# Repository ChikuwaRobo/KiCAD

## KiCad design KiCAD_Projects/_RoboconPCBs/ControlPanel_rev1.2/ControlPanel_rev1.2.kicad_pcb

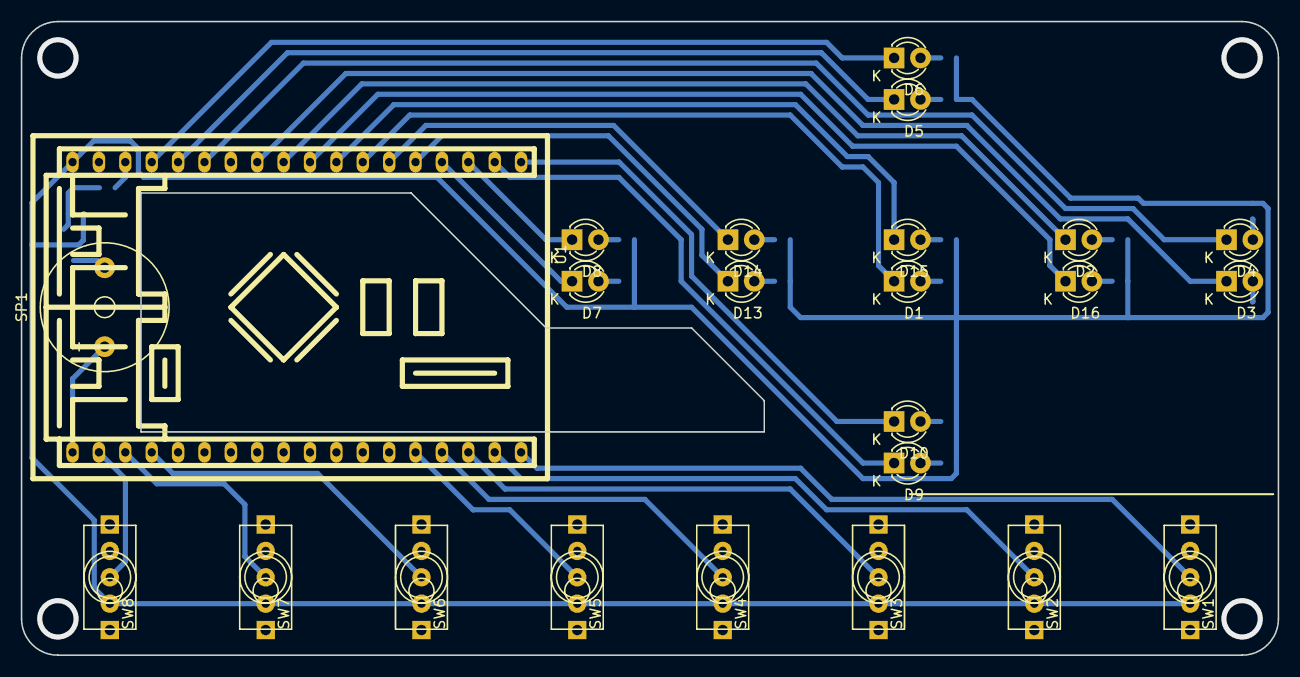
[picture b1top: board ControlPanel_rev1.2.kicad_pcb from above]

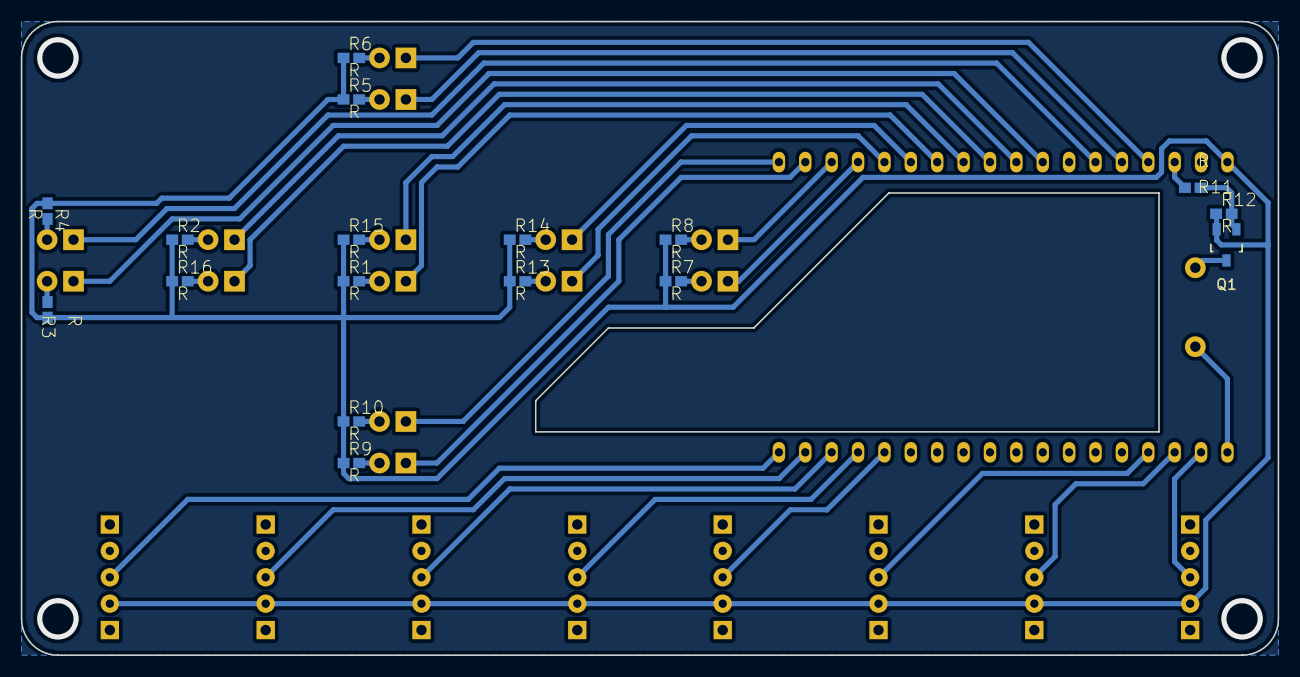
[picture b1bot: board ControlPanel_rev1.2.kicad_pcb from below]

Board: 2 copper layers, 121.0 x 61.0 mm, 41 parts (17 on the bottom side), 41 nets.

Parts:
D1, D2, D3, D4, D5, D6, D7, D8, D9, D10, D13, D14, D15, D16: LED; LED-3MM
Q1: MOSFET_N; SOT-23_Handsoldering
R1, R2, R3, R4, R5, R6, R7, R8, R9, R10, R11, R12, R13, R14, R15, R16: R; C1608_NP
SP1: SPEAKER; Buzzer_12x9.5RM7.6
SW1, SW2, SW3, SW4, SW5, SW6, SW7, SW8: SWITCH_INV; SW_toggle_3P
U1: F103_mini_rev1.1; F103_mini

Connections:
+12V: SP1.1, U1.19
/BUZZER: R11.2, U1.16
/TOGGLE_A: SW1.2, U1.36
/TOGGLE_B: SW2.2, U1.35
/TOGGLE_C: SW3.2, U1.34
/TOGGLE_D: SW4.2, U1.33
/TOGGLE_E: SW5.2, U1.32
/TOGGLE_F: SW6.2, U1.22
/TOGGLE_G: SW7.2, U1.21
/TOGGLE_H: SW8.2, U1.20
GND: Q1.S, R1.1, R2.1, R3.1, R4.1, R5.1, R6.1, R7.1, R8.1, R9.1, R10.1, R12.1, R13.1, R14.1, R15.1, R16.1, SW1.3, SW2.3, SW3.3, SW4.3, SW5.3, SW6.3, SW7.3, SW8.3, U1.18
unnamed: D1.1, U1.7
unnamed: D1.2, R1.2
unnamed: D2.1, U1.10
unnamed: D2.2, R2.2
unnamed: D3.1, U1.11
unnamed: D3.2, R3.2
unnamed: D4.1, U1.13
unnamed: D4.2, R4.2
unnamed: D5.1, U1.14
unnamed: D5.2, R5.2
unnamed: D6.1, U1.15
unnamed: D6.2, R6.2
unnamed: D7.1, U1.4
unnamed: D7.2, R7.2
unnamed: D8.1, U1.3
unnamed: D8.2, R8.2
unnamed: D9.1, U1.2
unnamed: D9.2, R9.2
unnamed: D10.1, U1.1
unnamed: D10.2, R10.2
unnamed: D13.1, U1.5
unnamed: D13.2, R13.2
unnamed: D14.1, U1.6
unnamed: D14.2, R14.2
unnamed: D15.1, U1.8
unnamed: D15.2, R15.2
unnamed: D16.1, U1.9
unnamed: D16.2, R16.2
unnamed: Q1.D, SP1.2
unnamed: Q1.G, R11.1, R12.2

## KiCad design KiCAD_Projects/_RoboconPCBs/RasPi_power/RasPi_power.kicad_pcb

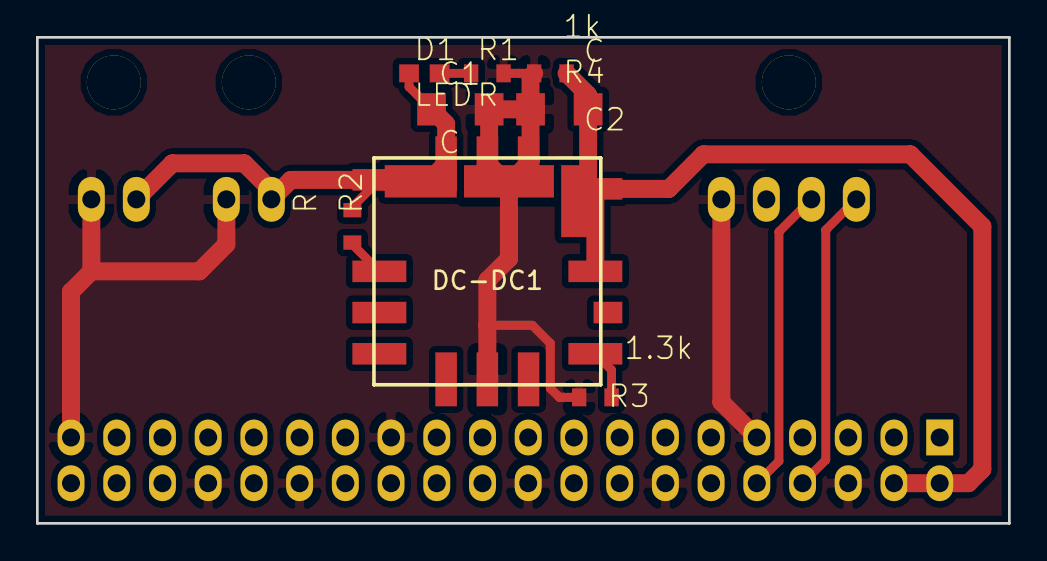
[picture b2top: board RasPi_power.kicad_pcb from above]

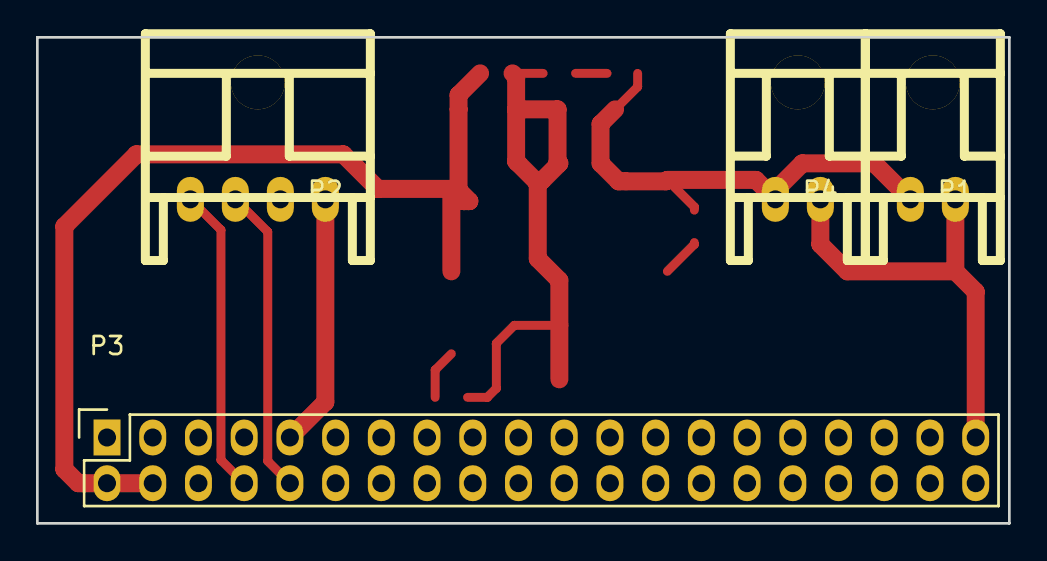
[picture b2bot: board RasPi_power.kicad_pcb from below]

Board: 2 copper layers, 54.0 x 27.0 mm, 12 parts (4 on the bottom side), 9 nets.

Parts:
C1, C2: C; C3216
D1: LED; C1608
DC-DC1: OKL-T3_series; OKL_T6
P1, P4: CONN_01X02; XA_2LC
P2: CONN_01X04; XA_4LC
P3: CONN_02X20; Socket_Strip_Straight_2x20
R1, R2: R; C1608_WP
R3: 1.3k; C1608_WP
R4: 1k; C1608_WP

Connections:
/3.3V: P3.1, P3.17
/5V: C2.1, DC-DC1.4, DC-DC1.5, P3.2, P3.4, R4.1
/12V: C1.1, D1.1, DC-DC1.2, P1.2, P4.2, R2.1
/GND: C1.2, C2.2, DC-DC1.3, DC-DC1.7, P1.1, P2.1, P3.6, P3.9, P3.14, P3.20, P3.25, P3.30, P3.34, P3.39, P4.1, R1.2, R3.2, R4.2
/GPIO14: P2.4, P3.8
/GPIO15: P2.3, P3.10
unnamed: D1.2, R1.1
unnamed: DC-DC1.1, R2.2
unnamed: DC-DC1.6, R3.1

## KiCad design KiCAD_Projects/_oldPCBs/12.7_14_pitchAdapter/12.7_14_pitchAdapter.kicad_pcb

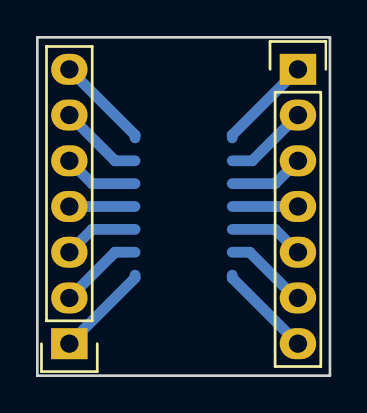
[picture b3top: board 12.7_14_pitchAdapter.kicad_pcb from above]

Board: 2 copper layers, 16.3 x 18.8 mm, 3 parts (1 on the bottom side), 14 nets.

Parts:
P1, P3: CONN_01X07; Pin_Header_Straight_1x07
P2: DIL14; SOIC-14_3.9x8.7mm_Pitch1.27mm

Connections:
unnamed: P1.1, P2.1
unnamed: P1.2, P2.2
unnamed: P1.3, P2.3
unnamed: P1.4, P2.4
unnamed: P1.5, P2.5
unnamed: P1.6, P2.6
unnamed: P1.7, P2.7
unnamed: P2.8, P3.1
unnamed: P2.9, P3.2
unnamed: P2.10, P3.3
unnamed: P2.11, P3.4
unnamed: P2.12, P3.5
unnamed: P2.13, P3.6
unnamed: P2.14, P3.7

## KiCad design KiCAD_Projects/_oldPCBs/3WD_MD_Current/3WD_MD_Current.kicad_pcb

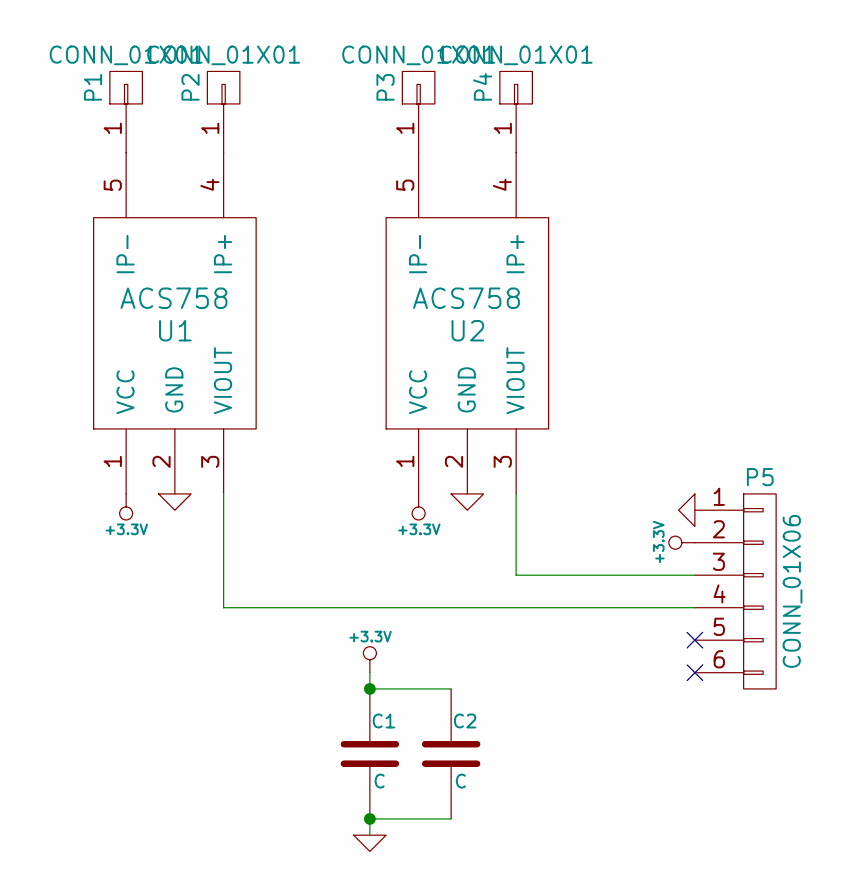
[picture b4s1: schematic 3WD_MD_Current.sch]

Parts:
C1, C2: C; C1608_WP
P1, P2, P3, P4: CONN_01X01; 1pin
P5: CONN_01X06; Pin_Header_Straight_1x06
U1, U2: ACS758; ACS785xCB

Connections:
+3.3V: C1.1, C2.1, P5.2, U1.1 (VCC), U2.1 (VCC)
GND: C1.2, C2.2, P5.1, U1.2 (GND), U2.2 (GND)
unnamed: P1.1, U1.5 (IP-)
unnamed: P2.1, U1.4 (IP+)
unnamed: P3.1, U2.5 (IP-)
unnamed: P4.1, U2.4 (IP+)
unnamed: P5.3, U2.3 (VIOUT)
unnamed: P5.4, U1.3 (VIOUT)

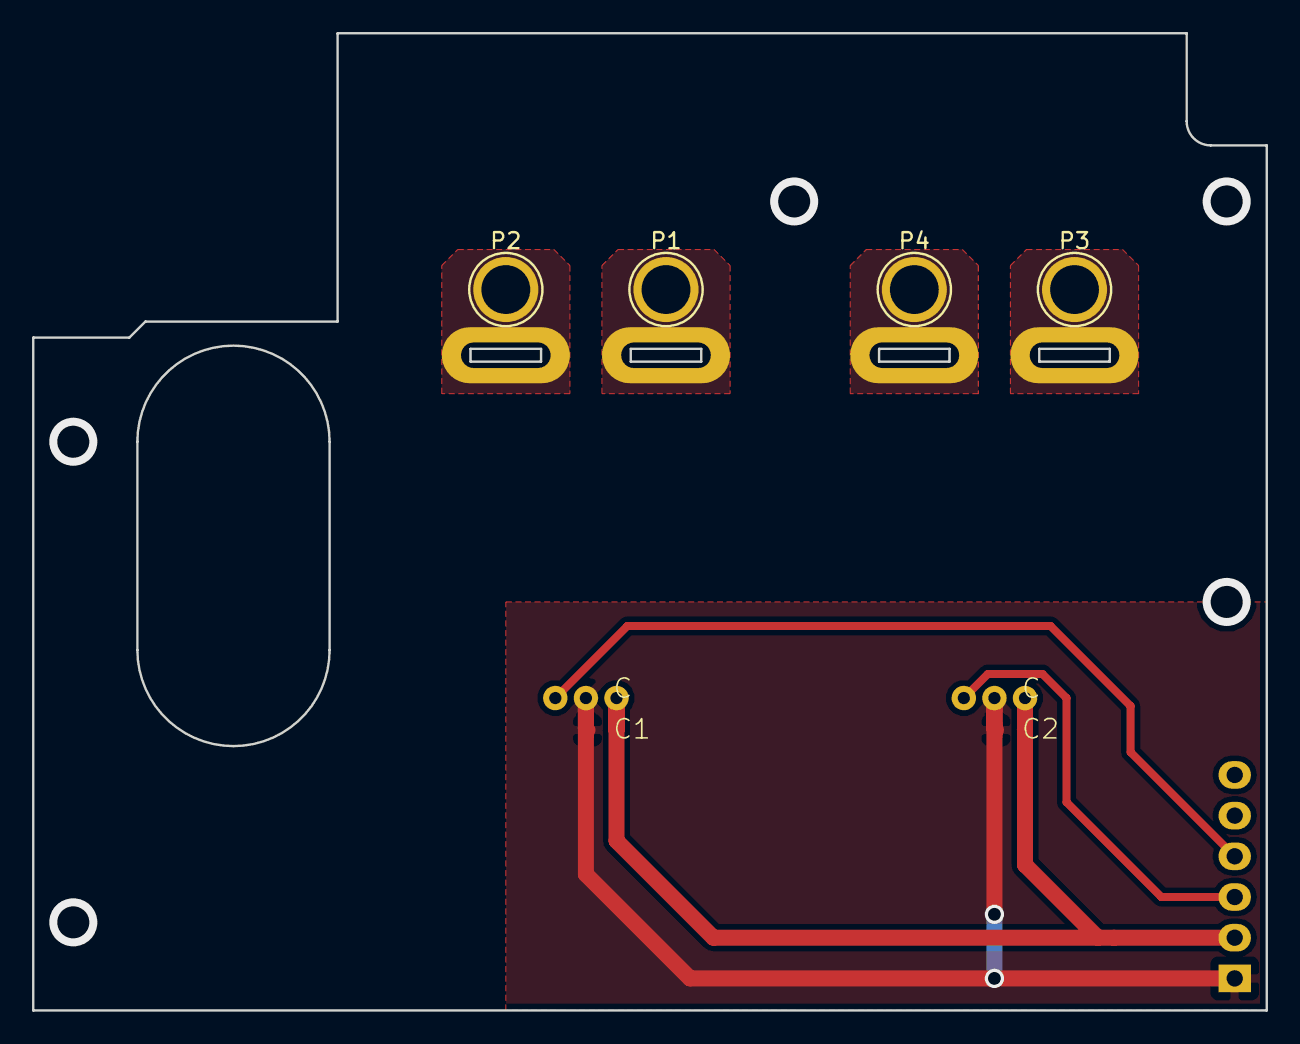
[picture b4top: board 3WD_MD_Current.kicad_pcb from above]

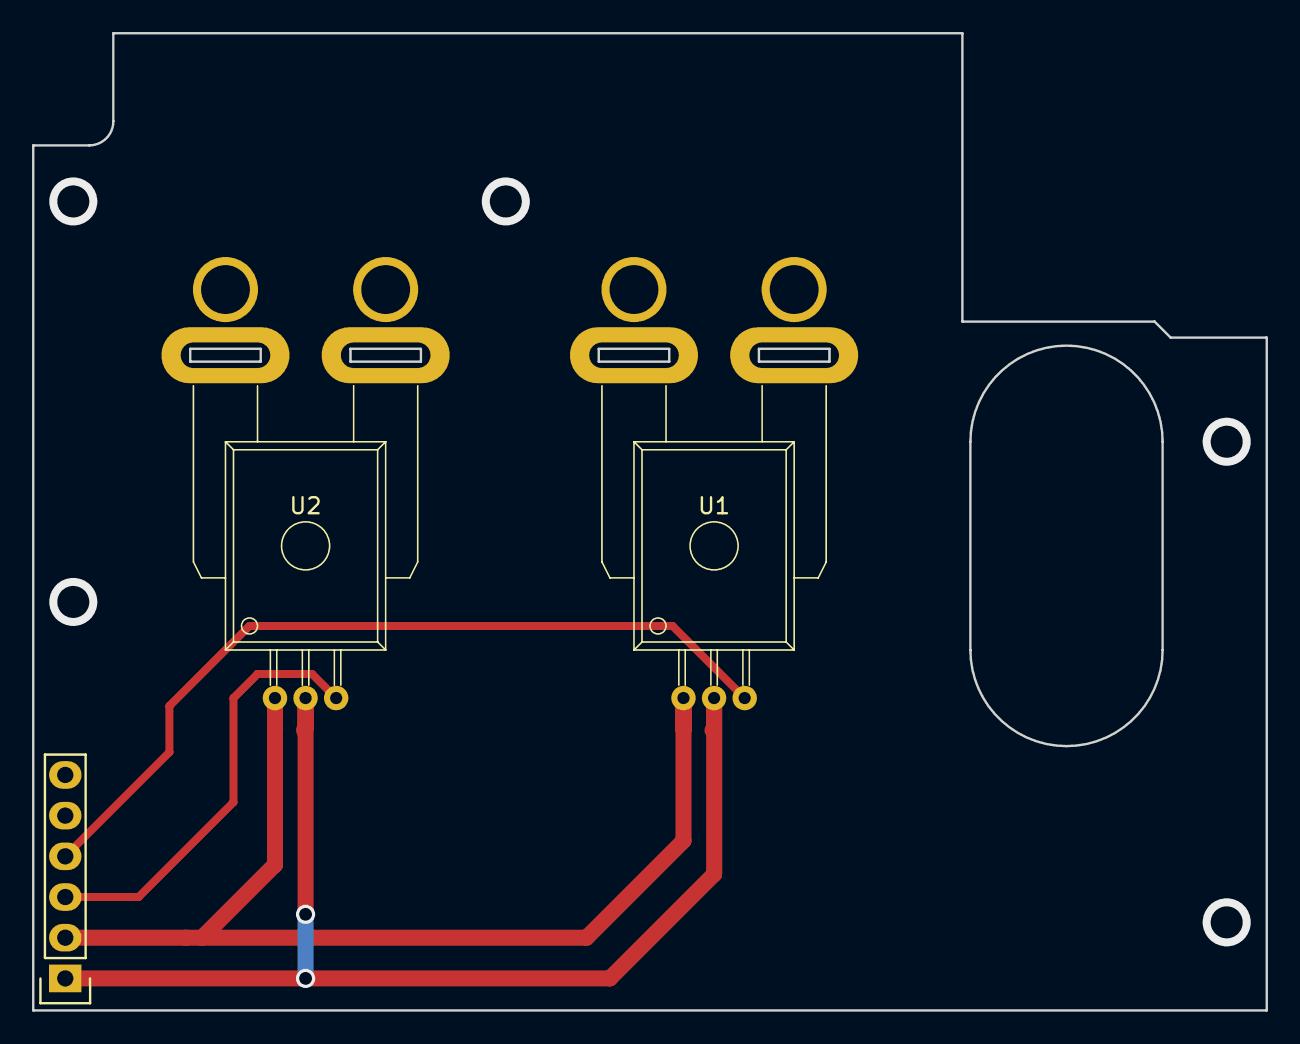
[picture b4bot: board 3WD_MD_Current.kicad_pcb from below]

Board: 2 copper layers, 77.0 x 61.0 mm, 9 parts (3 on the bottom side), 8 nets.

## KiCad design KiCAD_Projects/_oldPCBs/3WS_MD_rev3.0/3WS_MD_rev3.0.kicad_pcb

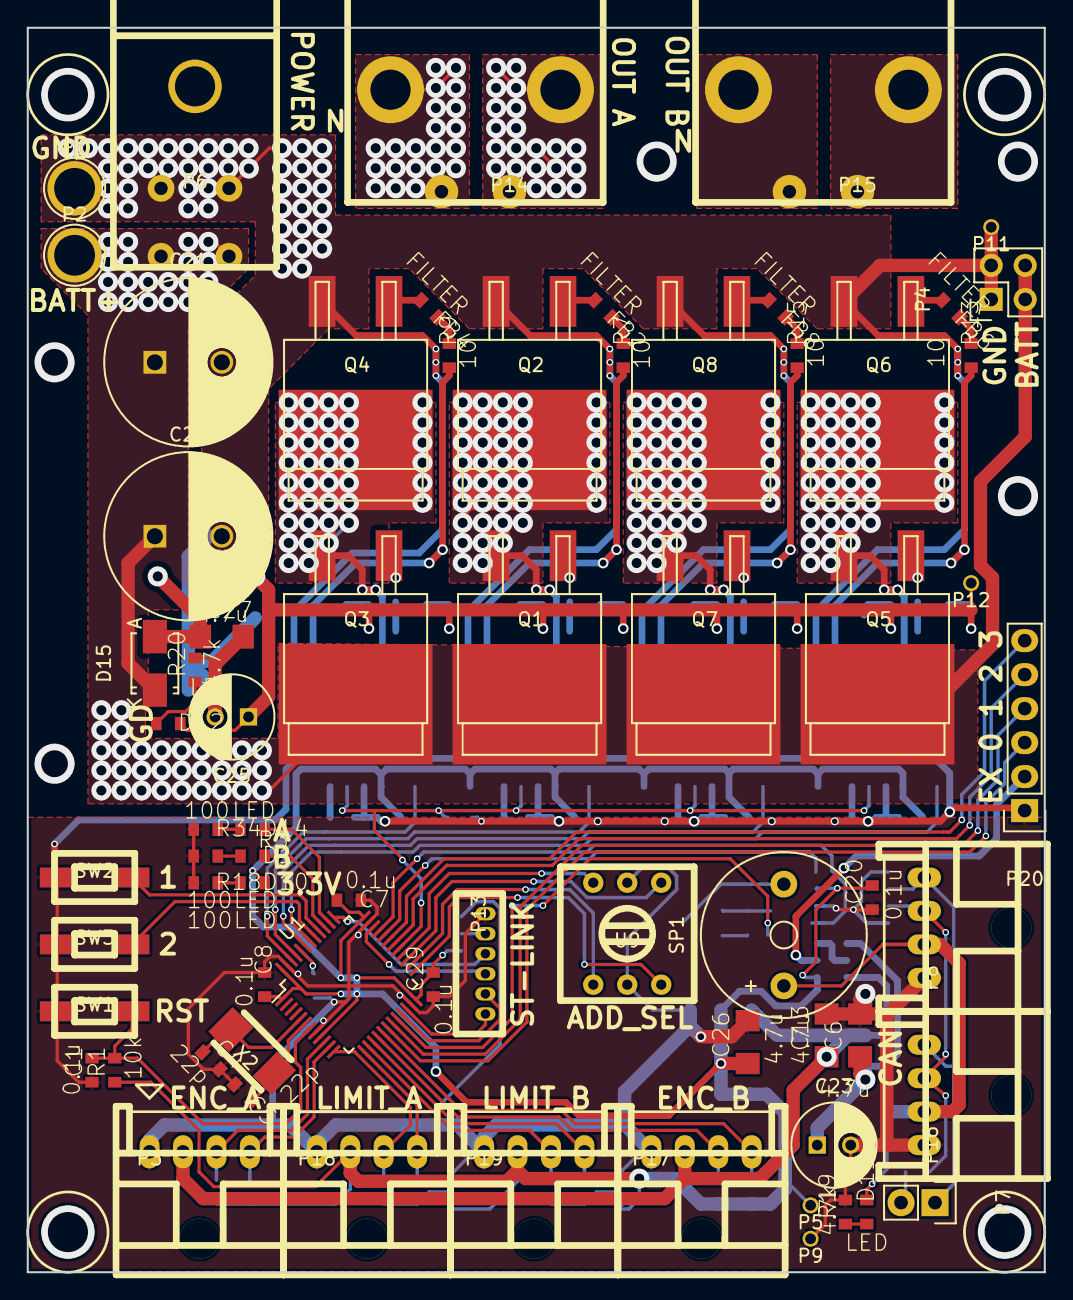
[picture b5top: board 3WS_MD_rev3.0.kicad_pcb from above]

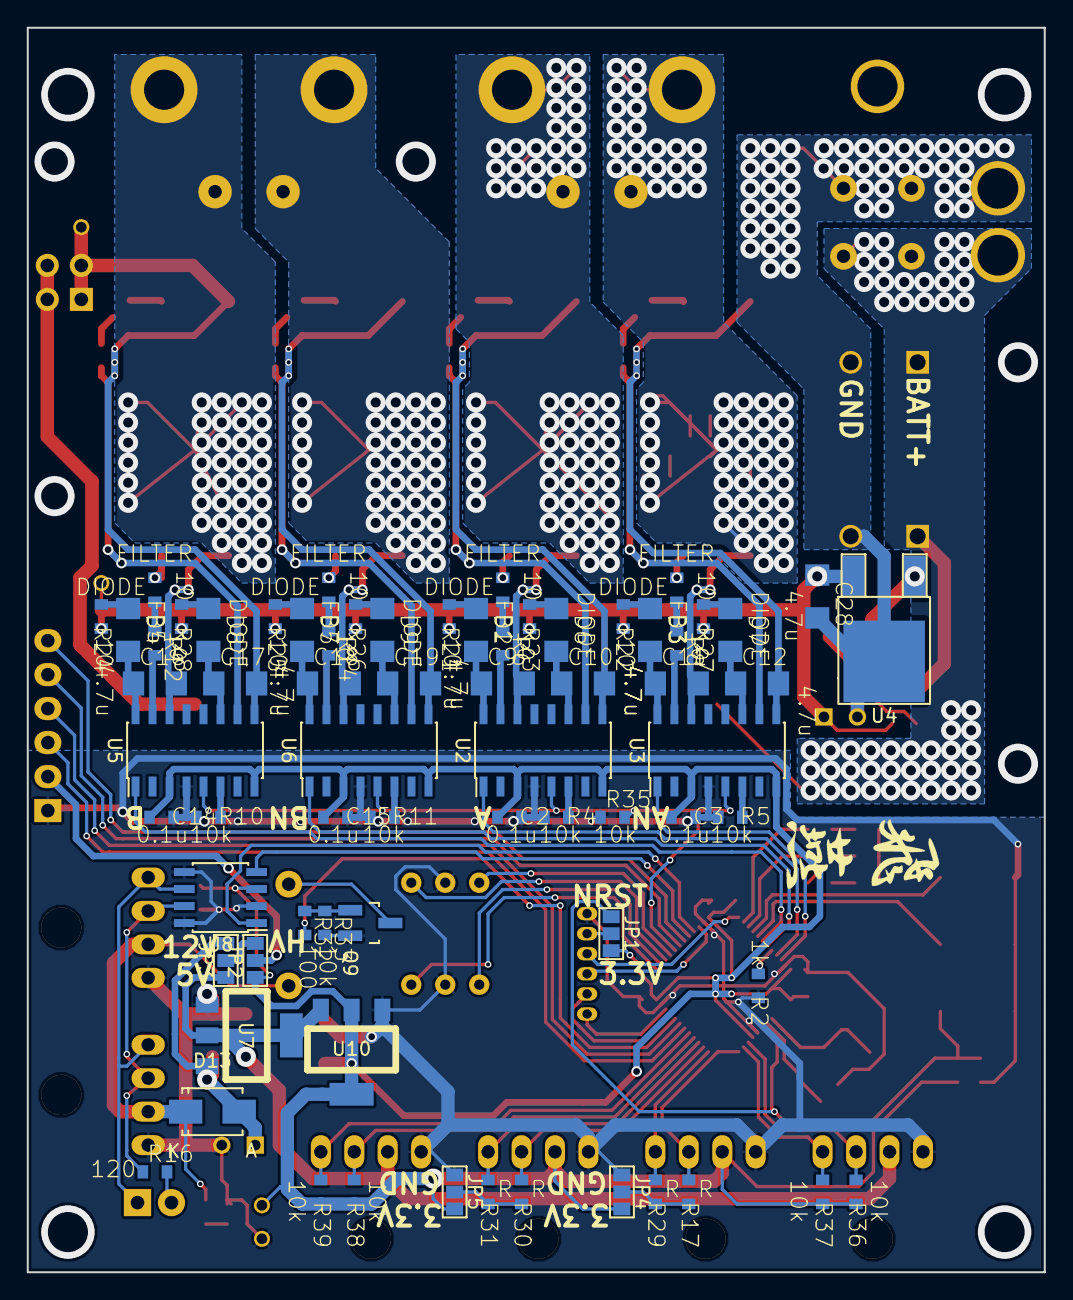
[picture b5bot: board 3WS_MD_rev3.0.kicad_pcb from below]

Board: 2 copper layers, 76.0 x 93.0 mm, 138 parts (69 on the bottom side), 108 nets.

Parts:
C1, C2, C3, C7, C8, C14, C15, C20, C29: 0.1u; C1608_WP
C4, C5: 22p; C1608_WP
C6, C9, C10, C11, C12, C13, C16, C17, C18, C19, C26, C27, C28: 4.7u; C3216
C21, C22: 470u; C_Radial_D12.5_L25_P5
C23, C25: 100u; C_Radial_D6.3_L11.2_P2.5
D1, D10, D11, D12, D14: LED; C1608_WP
D2, D3, D4, D5, D6, D7, D8, D9: DIODE; C3216
D13, D15: DIODE; SMA_Standard
FB1, FB2, FB3, FB4, FB5, FB6, FB7, FB8: FILTER; C1608_WP
JP1, JP2, JP3, JP4, JP5: JUMPER3; GS3
P1, P2: CONN_01X01; 1pin
P3, P8, P16, P17, P18, P19: CONN_01X04; XA_4LC
P4: CONN_02X02; Socket_Strip_Straight_2x02
P5, P9, P11, P12: TST; testPin
P6: CONN_01X04; D-3500D_4S
P7: CONN_01X02; Pin_Header_Straight_1x02
P13: CONN_01X06; ZH_6T
P14, P15: CONN_01X02; D-3200S_2L_PW
P20: CONN_01X06; Pin_Header_Straight_1x06
Q1, Q2, Q3, Q4, Q5, Q6, Q7, Q8: MOSFET_N; D2-PAK
Q9: MOSFET_N; SOT-23_Handsoldering
R1, R4, R5, R10, R11, R33, R35, R36, R37, R38, R39: 10k; C1608_WP
R2: 1k; C1608_WP
R3, R18, R32, R34: 100; C1608_WP
R6, R7, R8, R9, R12, R13, R14, R15, R21, R22, R23, R24, R25, R26, R27, R28: 10; C1608_WP
R16: 120; C1608_WP
R17, R29, R30, R31: R; C1608_WP
R19, R20: 4.7k; C1608_WP
SP1: SPEAKER; Buzzer_12x9.5RM7.6
SW1, SW2, SW3: SW_PUSH; RP_SMD_Button
U1: STM32F103_48; LQFP-48_7x7mm_Pitch0.5mm
U2, U3, U5, U6: SI8234; SOIC-16_3.9x9.9mm_Pitch1.27mm
U4: LM7812; TO-252-2Lead_regu
U7, U10: NCP1117ST33T3G; SOT-223_reg
U8: MAX3051; SOIC-8_3.9x4.9mm_Pitch1.27mm
U9: SW_ROTARY_16; rotary_0F
X2: CRYSTAL; ABM3_2pads

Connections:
+3.3V: C2.2, C3.2, C7.2, C8.2, C14.2, C15.2, C20.2, C26.1, C29.2, D10.1, JP1.3, JP2.1, JP4.3, JP5.3, P5.1, P18.2, P19.2, R1.1, R36.1, R37.1, R38.1, R39.1, U1.1, U1.9, U1.24, U1.36, U1.48, U2.3, U2.8, U3.3, U3.8, U5.3, U5.8, U6.3, U6.8, U8.3, U10.2
+5V: C13.1, JP3.1, P3.2, P17.2, U7.2, U10.3
+12V: D11.1, D13.1, P8.2, P16.2, SP1.1
+BATT: C21.1, C22.1, D15.1, P2.1, P4.2, P4.4, P6.2, P6.4, Q1.D, Q3.D, Q5.D, Q7.D
/BOOT0: R2.2, U1.44
/BUZZER: R32.2, U1.20
/CANH: P8.3, P16.3, R16.1, U8.7
/CANL: P7.1, P8.4, P16.4, U8.6
/CAN_RX: U1.32, U8.4
/CAN_TX: U1.33, U8.1
/ENC_Aa: P3.3, R36.2, U1.10
/ENC_Ab: P3.4, R37.2, U1.11
/ENC_Ba: P17.3, R38.2, U1.16
/ENC_Bb: P17.4, R39.2, U1.17
/EXIO_0: P20.3, U1.18
/EXIO_1: P20.4, U1.19
/EXIO_2: P20.5, U1.30
/EXIO_3: P20.6, U1.31
/GD_12V: C25.1, C28.1, D12.1, P12.1, R21.1, R22.1, R23.1, R24.1, R25.1, R26.1, R27.1, R28.1, U4.VO
/LED_A: D14.1, U1.38
/LED_B: D1.1, U1.39
/LIMIT_A1: P18.3, R17.2, U1.12
/LIMIT_A2: P18.4, R29.2, U1.13
/LIMIT_B1: P19.3, R30.2, U1.14
/LIMIT_B2: P19.4, R31.2, U1.15
/MOTOR_EN: R35.2, U1.29, U2.5, U3.5, U5.5, U6.5
/NRST: C1.2, JP1.1, R1.2, SW1.2, U1.7
/OSC_IN: C4.1, U1.5, X2.1
/OSC_OUT: C5.1, U1.6, X2.2
/OUT_A: C9.2, P14.1, Q1.S, Q2.D, U2.14
/OUT_AN: C11.2, P14.2, Q3.S, Q4.D, U3.14
/OUT_B: C16.2, P15.1, Q5.S, Q6.D, U5.14
/OUT_BN: C18.2, P15.2, Q7.S, Q8.D, U6.14
/PWM_A: U1.45, U2.1
/PWM_AN: U1.46, U3.1
/PWM_B: U1.42, U5.1
/PWM_BN: U1.43, U6.1
/SEL_1: U1.25, U9.3
/SEL_2: U1.26, U9.1
/SEL_4: U1.27, U9.4
/SEL_8: U1.28, U9.6
/SW1: SW2.2, U1.40
/SW2: SW3.2, U1.41
/SWCLK: P13.3, U1.37
/SWDIO: P13.4, U1.34
/USART_RX: P13.6, U1.22
/USART_TX: P13.5, U1.21
GND: C1.1, C2.1, C3.1, C4.2, C5.2, C6.2, C7.1, C8.1, C13.2, C14.1, C15.1, C20.1, C23.2, C26.2, C29.1, JP4.1, JP5.1, P3.1, P8.1, P9.1, P13.1, P16.1, P17.1, P18.1, P19.1, P20.1, Q9.S, R2.1, R3.2, R4.2, R5.2, R10.2, R11.2, R18.2, R19.2, R33.2, R34.2, R35.1, SW1.1, SW2.1, SW3.1, U1.8, U1.23, U1.35, U1.47, U2.4, U3.4, U5.4, U6.4, U7.1, U8.2, U8.5, U8.8, U9.2, U9.5, U10.1
GNDPWR: C10.2, C12.2, C17.2, C19.2, C21.2, C22.2, C25.2, C27.2, C28.2, P1.1, P4.1, P4.3, P6.1, P6.3, P11.1, Q2.S, Q4.S, Q6.S, Q8.S, R20.2, U2.9, U3.9, U4.GND, U5.9, U6.9
unnamed: C9.1, D2.2, U2.16
unnamed: C10.1, D6.2, U2.11
unnamed: C11.1, D3.2, U3.16
unnamed: C12.1, D7.2, U3.11
unnamed: C16.1, D4.2, U5.16
unnamed: C17.1, D8.2, U5.11
unnamed: C18.1, D5.2, U6.16
unnamed: C19.1, D9.2, U6.11
unnamed: C6.1, C23.1, D13.2, JP3.3, U7.3
unnamed: C27.1, D15.2, U4.VI
unnamed: D1.2, R3.1
unnamed: D2.1, R21.2
unnamed: D3.1, R22.2
unnamed: D4.1, R24.2
unnamed: D5.1, R25.2
unnamed: D6.1, R23.2
unnamed: D7.1, R27.2
unnamed: D8.1, R28.2
unnamed: D9.1, R26.2
unnamed: D10.2, R18.1
unnamed: D11.2, R19.1
unnamed: D12.2, R20.1
unnamed: D14.2, R34.1
unnamed: FB1.1, R6.1
unnamed: FB1.2, Q1.G
unnamed: FB2.1, R7.1
unnamed: FB2.2, Q2.G
unnamed: FB3.1, R8.1
unnamed: FB3.2, Q3.G
unnamed: FB4.1, R9.1
unnamed: FB4.2, Q4.G
unnamed: FB5.1, R12.1
unnamed: FB5.2, Q5.G
unnamed: FB6.1, R13.1
unnamed: FB6.2, Q6.G
unnamed: FB7.1, R14.1
unnamed: FB7.2, Q7.G
unnamed: FB8.1, R15.1
unnamed: FB8.2, Q8.G
unnamed: JP1.2, P13.2
unnamed: JP2.2, P20.2
unnamed: JP2.3, JP3.2
unnamed: JP4.2, R17.1, R29.1
unnamed: JP5.2, R30.1, R31.1
unnamed: P7.2, R16.2
unnamed: Q9.D, SP1.2
unnamed: Q9.G, R32.1, R33.1
unnamed: R4.1, U2.6
unnamed: R5.1, U3.6
unnamed: R6.2, U2.15
unnamed: R7.2, U2.10
unnamed: R8.2, U3.15
unnamed: R9.2, U3.10
unnamed: R10.1, U5.6
unnamed: R11.1, U6.6
unnamed: R12.2, U5.15
unnamed: R13.2, U5.10
unnamed: R14.2, U6.15
unnamed: R15.2, U6.10
